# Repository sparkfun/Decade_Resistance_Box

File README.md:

Decade Resistance Box - KIT-13006
========================================

[ 
KIT-13006](https://www.sparkfun.com/products/13006)

This repository is for a decade resistance box kit, adjustable between 0 Ohms and 999,990 Ohms in 10 Ohm steps.  [More information can be found here.](https://www.sparkfun.com/products/13006)

Detailed information about building and using the decade resistance can be found it it's [hookup guide](https://learn.sparkfun.com/tutorials/decade-resistance-box-hookup-guide). 

This part was created in Eagle v6.5.0.  
The front panel etching/overlay was created with Inkscape 0.48.

Repository Contents
-------------------

* **/Hardware** - All Eagle design files (.brd, .sch, .STL)
* **/case-label** - The front panel markings in PDF and multi-layer SVG formats. 
* **/tutorial-images** - the sources for the images in the hookup guide. 

Product Versions
----------------
* [KIT-13006](https://www.sparkfun.com/products/13006)- Initial version of the kit PCBs.

Version History
---------------
* [ab37315990e0f04e8026698d327f7af8112845c8](https://github.com/sparkfun/Decade_Resistance_Box/commit/ab37315990e0f04e8026698d327f7af8112845c8) V10 PCB files 

License Information
-------------------
The hardware is released under [Creative Commons ShareAlike 4.0 International](https://creativecommons.org/licenses/by-sa/4.0/).

Distributed as-is; no warranty is given.

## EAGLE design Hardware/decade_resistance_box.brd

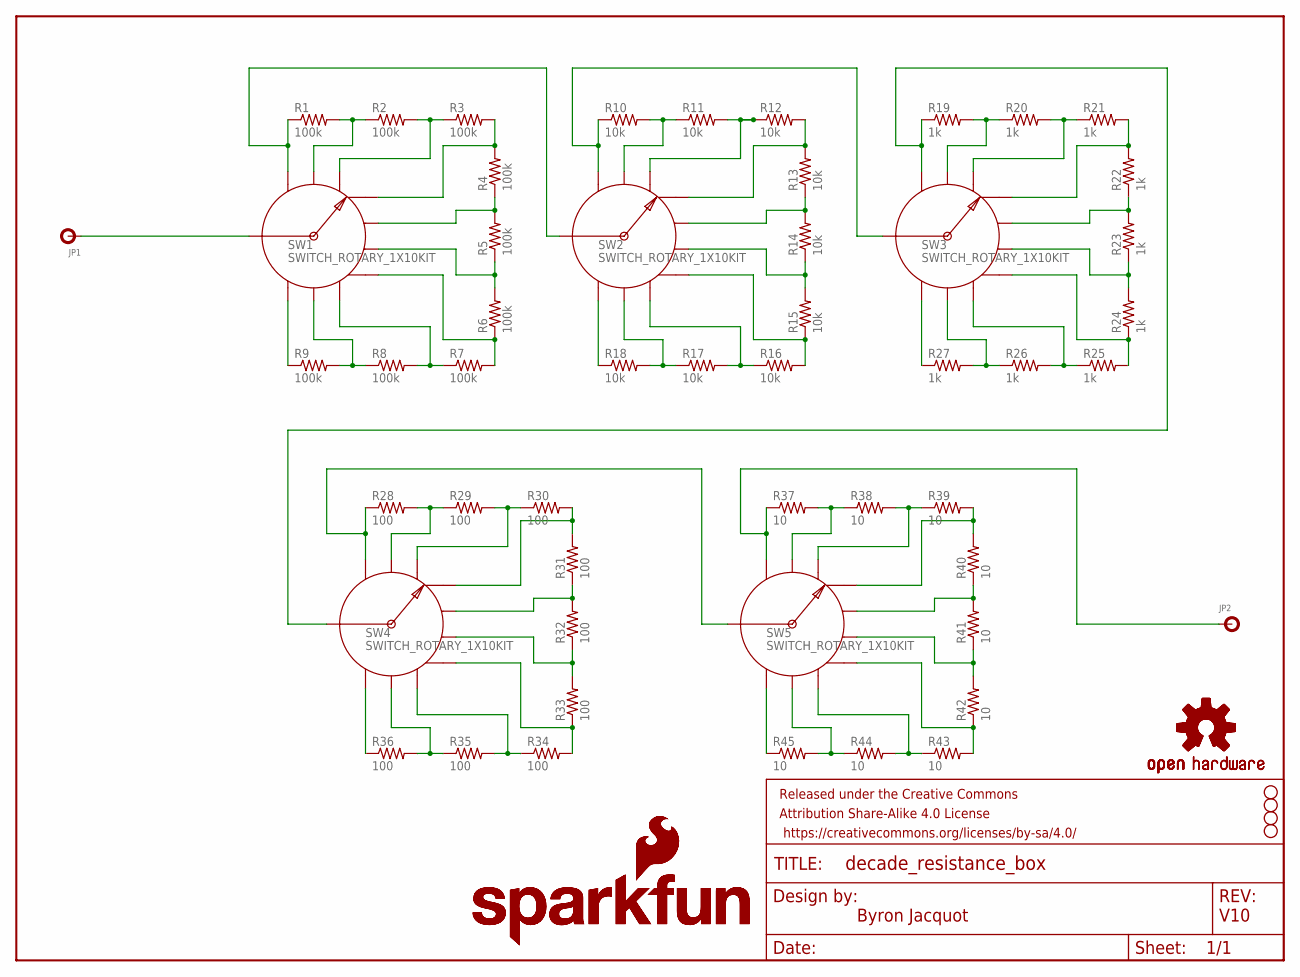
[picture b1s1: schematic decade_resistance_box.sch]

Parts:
FRAME1: FRAME-LETTER; CREATIVE_COMMONS
JP1, JP2: BANANA-JACK
LOGO1, LOGO4: OSHW-LOGOL; OSHW-LOGO-L
LOGO2: SFE_LOGO_NAME_FLAME.2_INCH; SFE_LOGO_NAME_FLAME_.2
LOGO3: SFE_LOGO_NAME_FLAME.5_INCH; SFE_LOGO_NAME_FLAME_.5
R1, R2, R3, R4, R5, R6, R7, R8, R9: 100k; AXIAL-0.1EZ
R10, R11, R12, R13, R14, R15, R16, R17, R18: 10k; AXIAL-0.1EZ
R19, R20, R21, R22, R23, R24, R25, R26, R27: 1k; AXIAL-0.1EZ
R28, R29, R30, R31, R32, R33, R34, R35, R36: 100; AXIAL-0.1EZ
R37, R38, R39, R40, R41, R42, R43, R44, R45: 10; AXIAL-0.1EZ
STANDOFF1, STANDOFF2, STANDOFF3, STANDOFF4: STAND-OFF
SW1, SW2, SW3, SW4, SW5: SWITCH_ROTARY_1X10KIT; ROTARY_SWITCH_1X10_KIT

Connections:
unnamed: R1.P$1 (1), SW1.1, SW2.COMMON
unnamed: R1.P$2 (2), R2.P$1 (1), SW1.2
unnamed: R2.P$2 (2), R3.P$1 (1), SW1.3
unnamed: R3.P$2 (2), R4.P$2 (2), SW1.4
unnamed: R4.P$1 (1), R5.P$2 (2), SW1.5
unnamed: R5.P$1 (1), R6.P$2 (2), SW1.6
unnamed: R6.P$1 (1), R7.P$2 (2), SW1.7
unnamed: R7.P$1 (1), R8.P$2 (2), SW1.8
unnamed: R8.P$1 (1), R9.P$2 (2), SW1.9
unnamed: R9.P$1 (1), SW1.10
unnamed: R10.P$1 (1), SW2.1, SW3.COMMON
unnamed: R10.P$2 (2), R11.P$1 (1), SW2.2
unnamed: R11.P$2 (2), R12.P$1 (1), SW2.3
unnamed: R12.P$2 (2), R13.P$2 (2), SW2.4
unnamed: R13.P$1 (1), R14.P$2 (2), SW2.5
unnamed: R14.P$1 (1), R15.P$2 (2), SW2.6
unnamed: JP1.P$1, SW1.COMMON
unnamed: R15.P$1 (1), R16.P$2 (2), SW2.7
unnamed: R16.P$1 (1), R17.P$2 (2), SW2.8
unnamed: R17.P$1 (1), R18.P$2 (2), SW2.9
unnamed: R18.P$1 (1), SW2.10
unnamed: R19.P$1 (1), SW3.1, SW4.COMMON
unnamed: R19.P$2 (2), R20.P$1 (1), SW3.2
unnamed: R20.P$2 (2), R21.P$1 (1), SW3.3
unnamed: R21.P$2 (2), R22.P$2 (2), SW3.4
unnamed: R22.P$1 (1), R23.P$2 (2), SW3.5
unnamed: R23.P$1 (1), R24.P$2 (2), SW3.6
unnamed: R24.P$1 (1), R25.P$2 (2), SW3.7
unnamed: R25.P$1 (1), R26.P$2 (2), SW3.8
unnamed: R26.P$1 (1), R27.P$2 (2), SW3.9
unnamed: R27.P$1 (1), SW3.10
unnamed: R28.P$1 (1), SW4.1, SW5.COMMON
unnamed: R28.P$2 (2), R29.P$1 (1), SW4.2
unnamed: R29.P$2 (2), R30.P$1 (1), SW4.3
unnamed: R30.P$2 (2), R31.P$2 (2), SW4.4
unnamed: R31.P$1 (1), R32.P$2 (2), SW4.5
unnamed: R32.P$1 (1), R33.P$2 (2), SW4.6
unnamed: R33.P$1 (1), R34.P$2 (2), SW4.7
unnamed: R34.P$1 (1), R35.P$2 (2), SW4.8
unnamed: R35.P$1 (1), R36.P$2 (2), SW4.9
unnamed: R36.P$1 (1), SW4.10
unnamed: JP2.P$1, R37.P$1 (1), SW5.1
unnamed: R37.P$2 (2), R38.P$1 (1), SW5.2
unnamed: R38.P$2 (2), R39.P$1 (1), SW5.3
unnamed: R39.P$2 (2), R40.P$2 (2), SW5.4
unnamed: R40.P$1 (1), R41.P$2 (2), SW5.5
unnamed: R41.P$1 (1), R42.P$2 (2), SW5.6
unnamed: R42.P$1 (1), R43.P$2 (2), SW5.7
unnamed: R43.P$1 (1), R44.P$2 (2), SW5.8
unnamed: R44.P$1 (1), R45.P$2 (2), SW5.9
unnamed: R45.P$1 (1), SW5.10

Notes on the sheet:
Byron Jacquot
V10

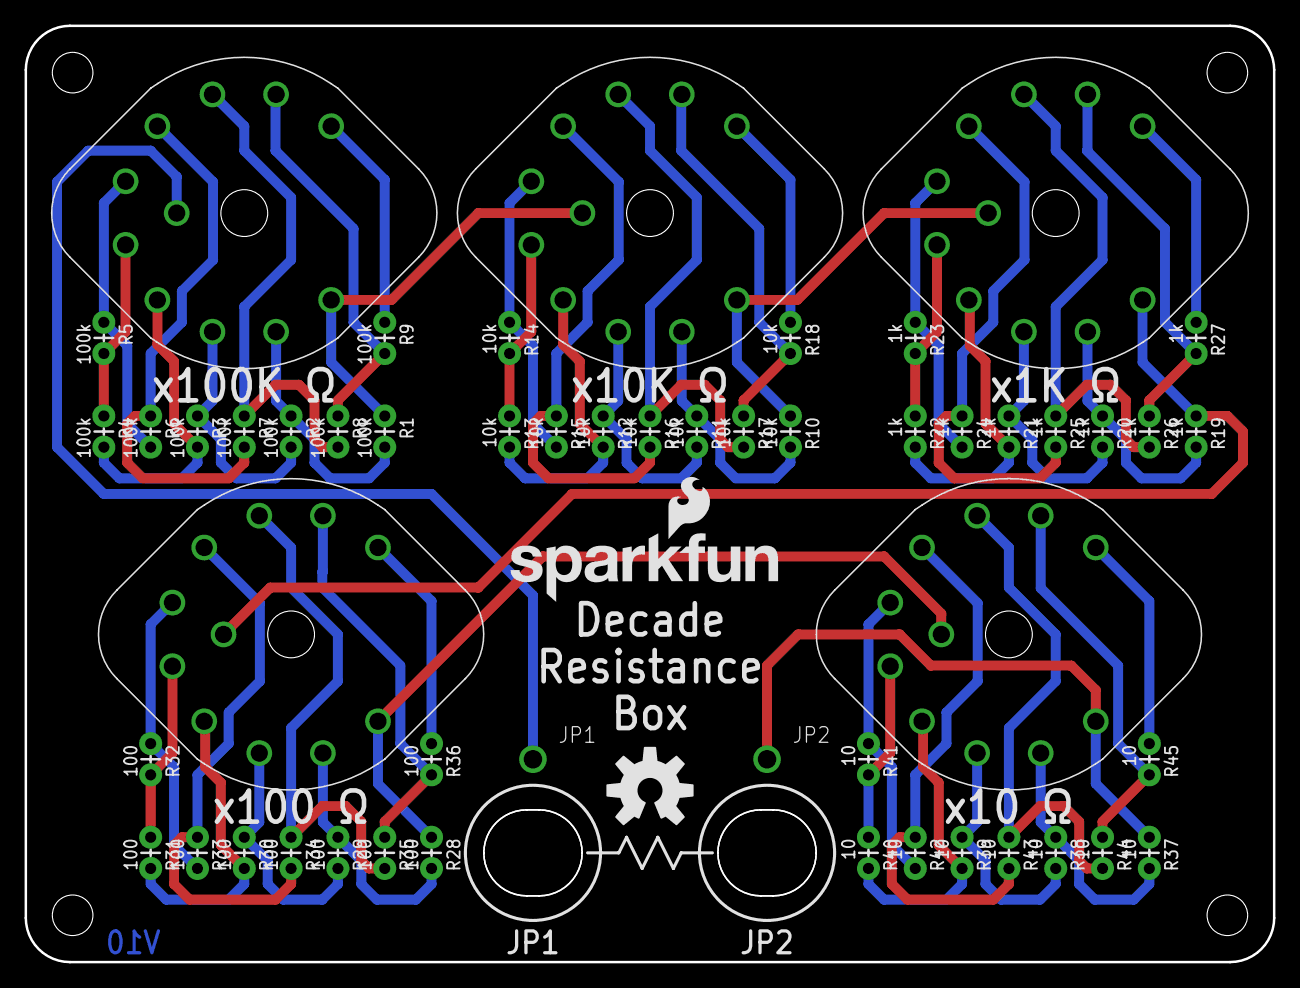
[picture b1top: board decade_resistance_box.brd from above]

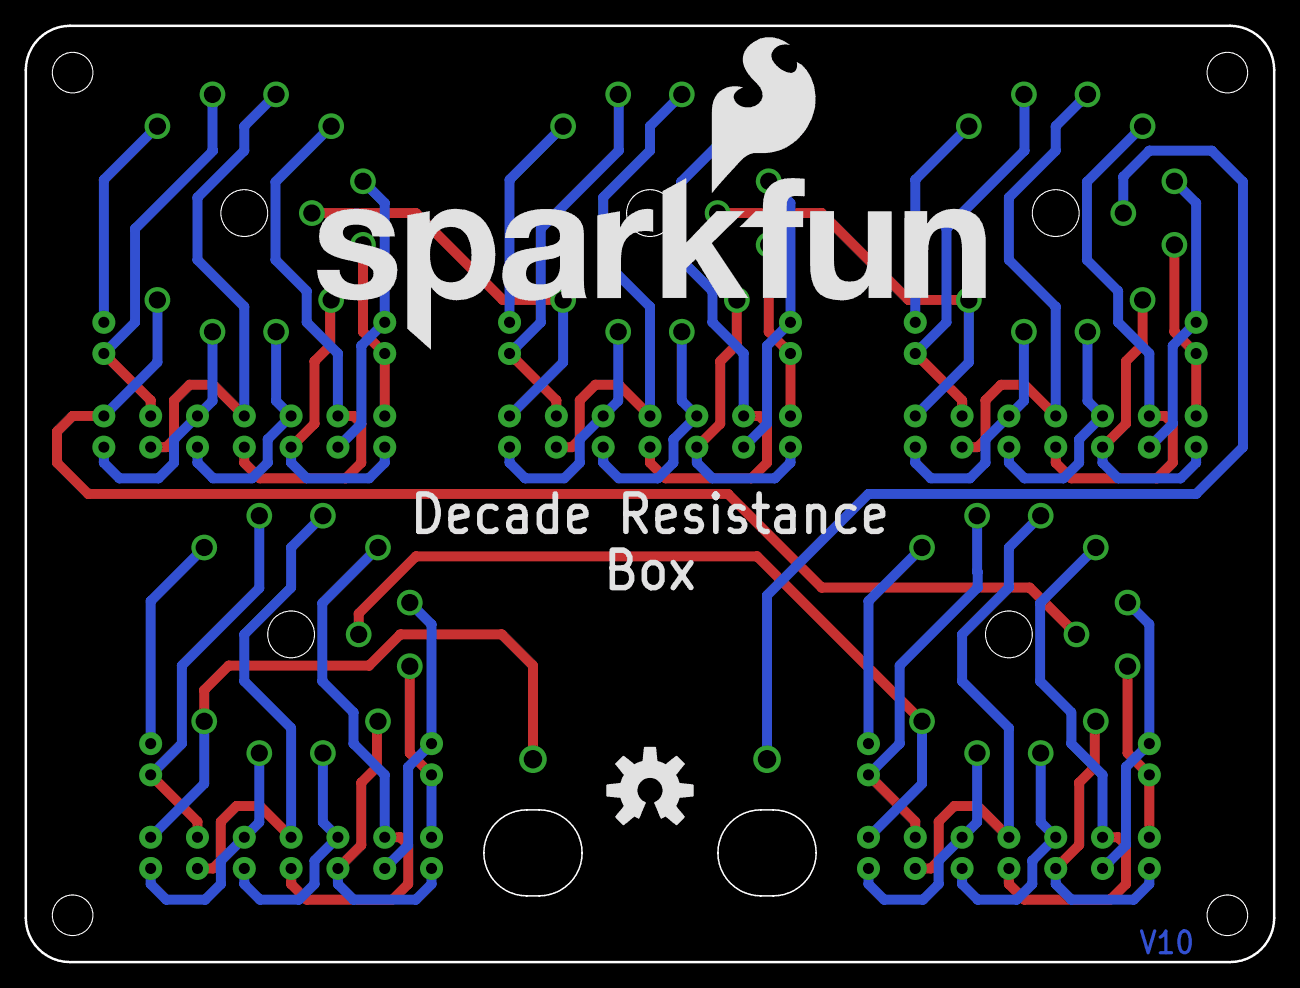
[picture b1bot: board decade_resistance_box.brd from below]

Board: 2 copper layers, 101.6 x 76.2 mm, 61 parts (2 on the bottom side), 51 nets.

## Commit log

2014-06-27 Initial commit
    PCB and boilderplate files
2014-06-30 Updated board after review
2014-07-01 Moving to new 1% resistors
2014-07-01 Updating rotaries
    Library part picked up PROD_ID and VALUE
2014-07-01 One more library update for switches
2014-08-05 Updates from Prototype review
2014-08-11 Updates following redboard review
    Added a couple more dimension markings
2014-11-24 Adding tutorial images
2014-11-26 Many more illustrations
2014-12-03 Updating readme for product launch
2014-12-03 More readme updates
2014-12-03 One more readme update
    Apparently Github doesn't have the magic the renders "&ohm;" as an
    omega...
2015-01-02 Some updates to the case labels.
    Some users have reported trouble opening the SVG, so I also saved it as
    a printable PDF.
2015-01-02 Updating readme with label changes.

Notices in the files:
parts and their libraries:
SparkFun-Aesthetics: Licensing: Creative Commons ShareAlike 4.0 International - https://creativecommons.org/licenses/by-sa/4.0
SparkFun-Aesthetics: Released under the Creative Commons Attribution Share-Alike 4.0 License
SparkFun-Aesthetics: Released under the Creative Commons
